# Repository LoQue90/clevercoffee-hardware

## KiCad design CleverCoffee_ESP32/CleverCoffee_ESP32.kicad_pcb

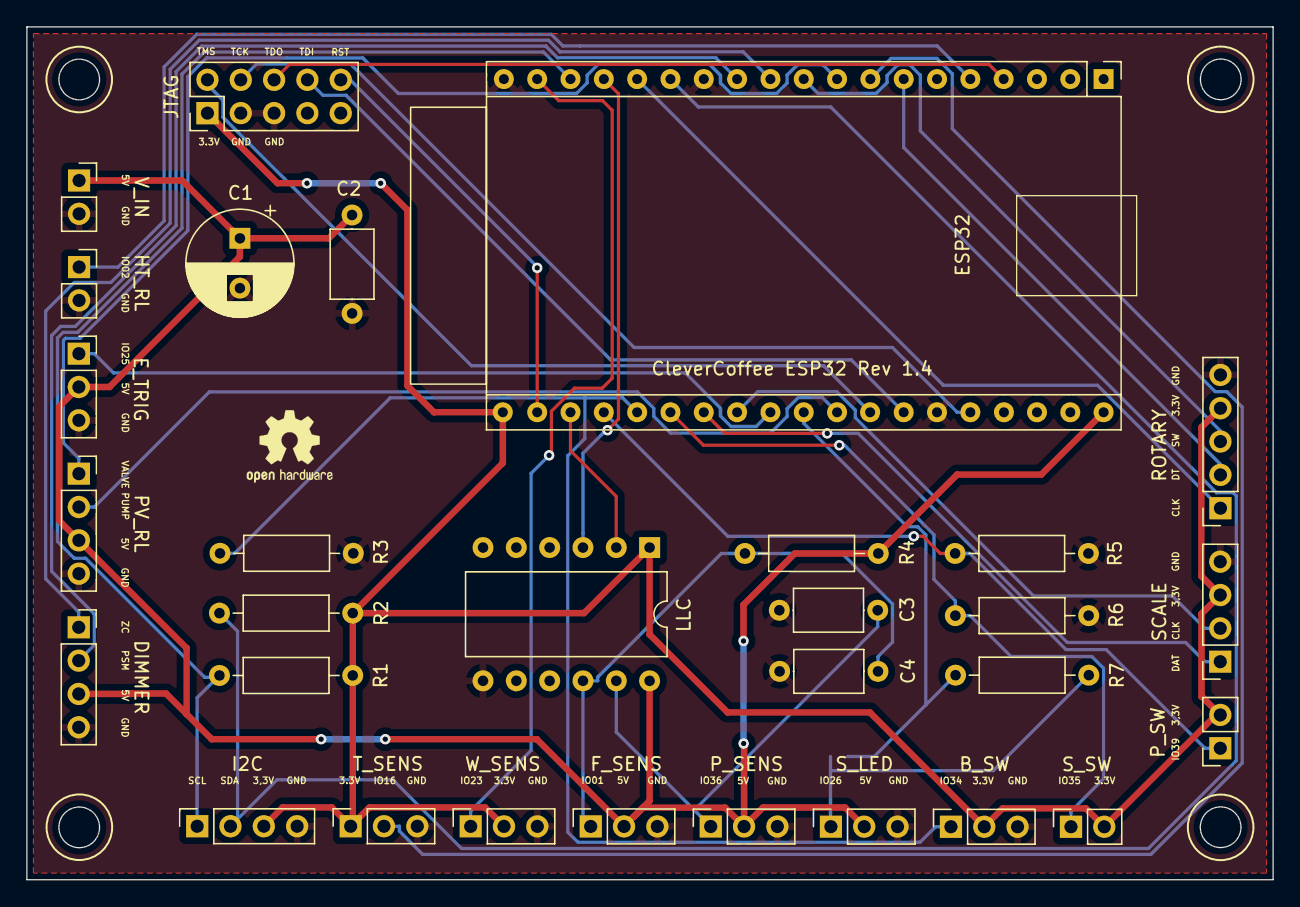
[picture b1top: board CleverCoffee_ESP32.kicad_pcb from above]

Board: 2 copper layers, 95.0 x 65.0 mm, 31 parts (1 on the bottom side), 32 nets.

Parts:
B_SW: Conn_01x03; PinSocket_1x03_P2.54mm_Vertical
C1: 220 μF; CP_Radial_D8.0mm_P3.80mm
C2, C3, C4: 100 nF; C_Axial_L5.1mm_D3.1mm_P7.50mm_Horizontal
DIMMER: Conn_01x04; PinSocket_1x04_P2.54mm_Vertical
ESP32: NodeMCU_DevKitC_v4; NodeMCU DevKitC v4
E_TRIG: Conn_01x03; PinSocket_1x03_P2.54mm_Vertical
F_SENS: Conn_01x03; PinSocket_1x03_P2.54mm_Vertical
HT_RL: Conn_01x02; PinSocket_1x02_P2.54mm_Vertical
I2C: Conn_01x04; PinSocket_1x04_P2.54mm_Vertical
JP1: SolderJumper_2_Open; SolderJumper-2_P1.3mm_Open_Pad1.0x1.5mm
JTAG: Conn_ARM_JTAG_SWD_10; PinHeader_2x05_P2.54mm_Vertical
LLC: TXB0104D_DIP; DIP-12_W10.16mm
PV_RL: Conn_01x04; PinSocket_1x04_P2.54mm_Vertical
P_SENS: Conn_01x03; PinSocket_1x03_P2.54mm_Vertical
P_SW: Conn_01x02; PinSocket_1x02_P2.54mm_Vertical
R1, R2, R4: 4K7 Ω; R_Axial_DIN0207_L6.3mm_D2.5mm_P10.16mm_Horizontal
R3, R5, R6: 47K Ω; R_Axial_DIN0207_L6.3mm_D2.5mm_P10.16mm_Horizontal
R7: 220 Ω; R_Axial_DIN0207_L6.3mm_D2.5mm_P10.16mm_Horizontal
ROTARY: Conn_01x05; PinSocket_1x05_P2.54mm_Vertical
SCALE: Conn_01x04; PinSocket_1x04_P2.54mm_Vertical
S_LED: Conn_01x03; PinSocket_1x03_P2.54mm_Vertical
S_SW: Conn_01x02; PinSocket_1x02_P2.54mm_Vertical
T_SENS: Conn_01x03; PinSocket_1x03_P2.54mm_Vertical
V_IN: Conn_01x02; PinSocket_1x02_P2.54mm_Vertical
W_SENS: Conn_01x03; PinSocket_1x03_P2.54mm_Vertical

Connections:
+3V3: B_SW.2, ESP32.20 (3V3), I2C.3, JTAG.1 (VTref), LLC.1 (VCCA), P_SW.2, R1.2, R2.2, ROTARY.4, SCALE.3, S_SW.2, T_SENS.1, W_SENS.2
+5V: C1.1, C2.1, DIMMER.3, ESP32.38 (VDD), E_TRIG.2, F_SENS.2, LLC.12 (VCCB), PV_RL.3, P_SENS.2, R4.1, S_LED.2, V_IN.1
F_SENS: C4.2, F_SENS.1, LLC.10 (B2), R4.2
GND: B_SW.3, C1.2, C2.2, C3.1, C4.1, DIMMER.4, ESP32.13 (GND), ESP32.19 (GND), ESP32.33 (GND), E_TRIG.3, F_SENS.3, HT_RL.2, I2C.4, JTAG.3 (GND), JTAG.5 (GND), LLC.7 (GND), PV_RL.4, P_SENS.3, R3.1, R5.1, R6.1, ROTARY.5, SCALE.4, S_LED.3, T_SENS.3, V_IN.2, W_SENS.3
IO1: ESP32.16 (IO1/Tx), LLC.3 (A2)
IO2: ESP32.5 (IO2), HT_RL.1
IO16: ESP32.8 (IO16/Rx2), T_SENS.2
IO23: ESP32.18 (IO23), W_SENS.1
IO25: ESP32.28 (IO25), E_TRIG.1
IO26: ESP32.29 (IO26), JP1.2 (B), R7.2
IO34: B_SW.1, ESP32.24 (IO34), R3.2
IO35: ESP32.25 (IO35), R6.2, S_SW.1
IO36: ESP32.22 (IO36), LLC.2 (A1)
IO39: ESP32.23 (IO39), P_SW.1, R5.2
unnamed: JP1.1 (A), R7.1, S_LED.1
PSM: DIMMER.2, ESP32.12 (IO19)
PUMP: ESP32.30 (IO27), PV_RL.2
P_SENS: C3.2, LLC.11 (B1), P_SENS.1
RST: ESP32.21 (RST), JTAG.10 (~RESET)
RT_CLK: ESP32.15 (IO3/Rx), ROTARY.1
RT_DT: ESP32.7 (IO4), ROTARY.2
RT_SW: ESP32.10 (IO5), ROTARY.3
SCL: ESP32.17 (IO22/SCL), I2C.1, R1.1
SC_CLK: ESP32.27 (IO33), SCALE.2
SC_DAT: ESP32.26 (IO32), SCALE.1
SDA: ESP32.14 (IO21/SDA), I2C.2, R2.1
TCK: ESP32.34 (IO13/TCK), JTAG.4 (SWDCLK/TCK)
TDI: ESP32.32 (IO12/TDI), JTAG.8 (NC/TDI)
TDO: ESP32.4 (IO15/TDO), JTAG.6 (SWO/TDO)
TMS: ESP32.31 (IO14/TMS), JTAG.2 (SWDIO/TMS)
VALVE: ESP32.9 (IO17/Tx2), PV_RL.1
ZC: DIMMER.1, ESP32.11 (IO18)

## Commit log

2023-02-20 Bugfix Labels Silkscreen
    S_LED change VCC to 5V
    E_TRIG change VCC to 5V
    W_SENS change IO36 to IO23
    GPIO change IO23 to IO36
    change all VCC to 3,3V
    change GPIO to IO Nummer
2023-02-20 Bugfix Lable Silkscreen
    E_TRIG change VCC to 5V
    P_SW change GND to 3,3V
    W_SENS change IO36 to IO23
    P_SENS change IO23 to IO36
    ROTRAY SWITCH CLK DT
    change all VCC to 3,3V
